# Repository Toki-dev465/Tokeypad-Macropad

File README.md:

# Important Note
My PCB design has a slight error as the 5V on MC is connected to the VCC of OLED. Using 5V may or may not work. It could potentially damage the microcontroller and the OLED. Flashing QMK is a big pain hence I also made CircuitPython KMK firmware. Will definitely try the QMK firmware when I have time. 
# Description
IBM Model M keyboard themed macropad with a rotary encoder for volume control, 6 keys and a 0.91 inch OLED display. 

# Challenges
It was my first ever electronics project. First time using KiCad, Fusion and QMK. I spent many hours just trying to figure out how to do something by Googling and watching tutorials on YouTube. I had to redesign my schematics, PCB and 3D model numerous times. 3D modeling was much harder than I anticipated at first. Even though I made many errors, I believe this shows my learning progress because you can't learn without making mistakes. 

# Specs/BOM

- 1x XIAO RP2040
- 1x SK6812 MINI Led
- 4x M3x16 Bolt
- 4x M3 Heatset
- 6x Cherry MX Switches
- 6x Blank DSA Keycaps
- 1x I2C OLED Display Module 0.91 Inch SSD1306
- 1x Rotary Encoder Module

| Schematic | PCB Design | 3D Model |
| :---: | :---: | :---: |
|  |  |  |
| *Circuit Diagram* | *Top/Bottom Layers* | *Fusion 360 Render* |

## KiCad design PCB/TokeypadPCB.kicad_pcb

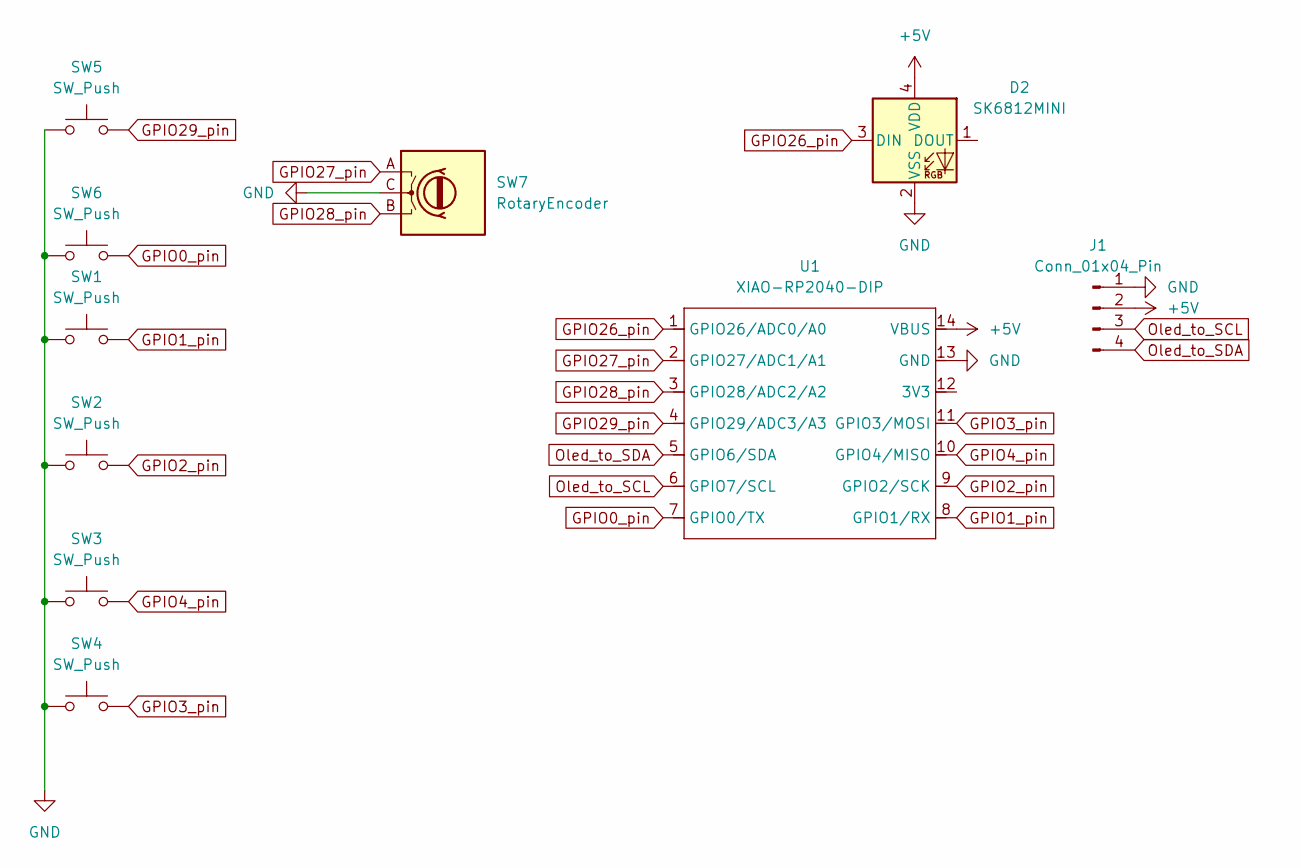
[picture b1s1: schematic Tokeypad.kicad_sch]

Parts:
D2: SK6812MINI; LED_SK6812MINI_PLCC4_3.5x3.5mm_P1.75mm
J1: Conn_01x04_Pin; NS-Tech_Grove_1x04_P2mm_Vertical
SW1, SW2, SW3, SW4, SW5, SW6: SW_Push; SW_Cherry_MX_1.00u_PCB
SW7: RotaryEncoder; RotaryEncoder_Alps_EC11E-Switch_Vertical_H20mm
U1: XIAO-RP2040-DIP

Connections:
+5V: D2.4 (VDD), J1.2, U1.14 (VBUS)
GND: D2.2 (VSS), J1.1, SW1.1, SW2.1, SW3.1, SW4.1, SW5.1, SW6.1, SW7.C, U1.13 (GND)
GPIO0_pin: SW6.2, U1.7 (GPIO0/TX)
GPIO1_pin: SW1.2, U1.8 (GPIO1/RX)
GPIO2_pin: SW2.2, U1.9 (GPIO2/SCK)
GPIO3_pin: SW4.2, U1.11 (GPIO3/MOSI)
GPIO4_pin: SW3.2, U1.10 (GPIO4/MISO)
GPIO26_pin: D2.3 (DIN), U1.1 (GPIO26/ADC0/A0)
GPIO27_pin: SW7.A, U1.2 (GPIO27/ADC1/A1)
GPIO28_pin: SW7.B, U1.3 (GPIO28/ADC2/A2)
GPIO29_pin: SW5.2, U1.4 (GPIO29/ADC3/A3)
Oled_to_SCL: J1.3, U1.6 (GPIO7/SCL)
Oled_to_SDA: J1.4, U1.5 (GPIO6/SDA)

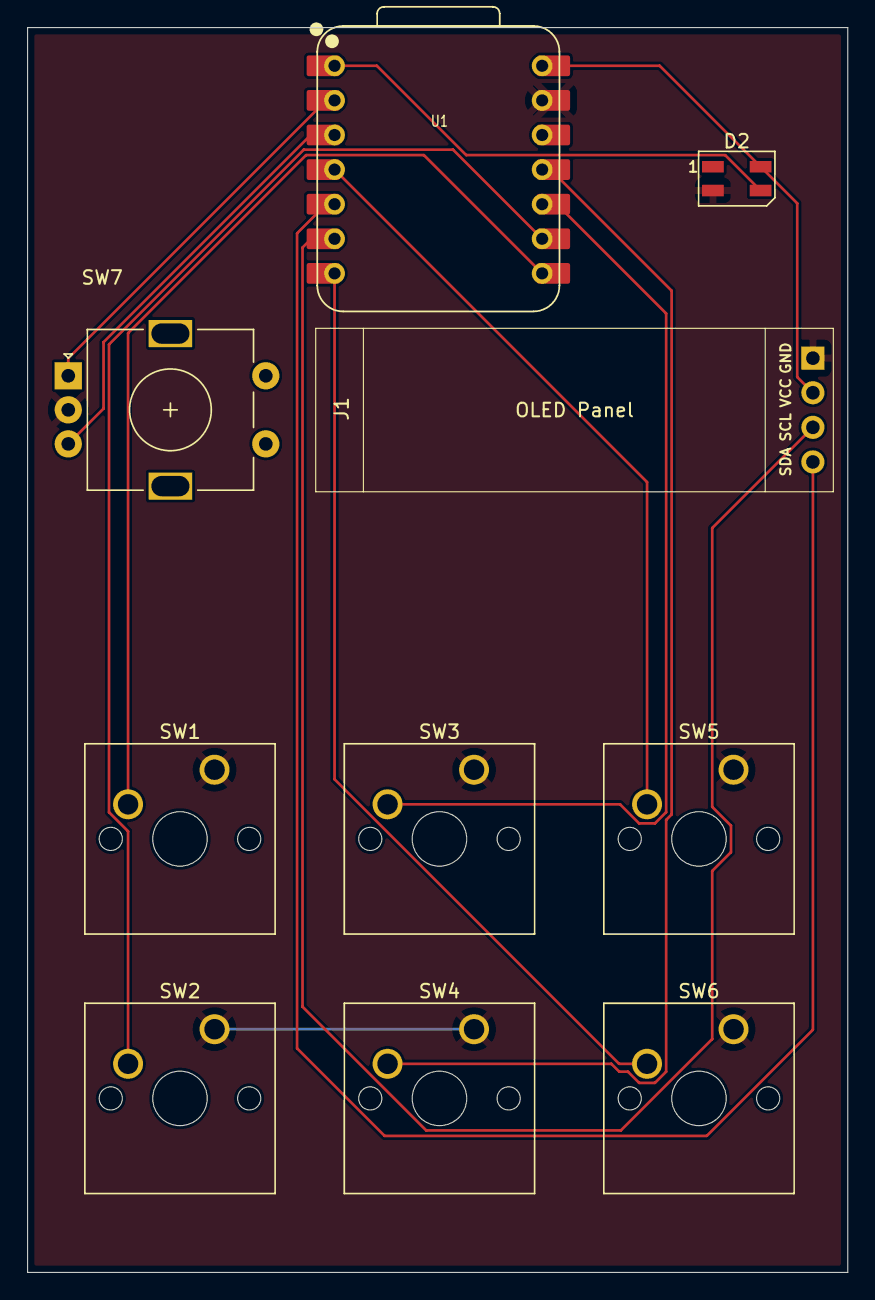
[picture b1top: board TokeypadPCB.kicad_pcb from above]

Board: 2 copper layers, 60.2 x 91.4 mm, 10 parts (0 on the bottom side), 13 nets.

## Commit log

2025-11-21 Create hardware
2025-11-21 Create Schematic
2025-11-21 Rename Screenshot 2025-11-20 224214.png to Hardware/Schematic
2025-11-21 Rename Screenshot 2025-11-20 224214.png to Hardware/Schematic 224214.png
2025-11-21 Rename Screenshot 2025-11-20 224214.png to Schematic.png
2025-11-21 Rename Schematic.png to Hardware/Schematic.png
2025-11-21 Rename Screenshot 2025-11-20 224214.png to Design/sketch.png
2025-11-21 Create Inspiration Model M
2025-12-23 Create Sketch
2025-12-23 Rename Macropad sketch.png to Design/Macropad sketch.png
2025-12-23 Create Design
2025-12-28 Created a new directory for only PCB related files for organization purposes
2026-02-01 Add files via upload
    Fixed version. Holes at the bottom for the screws were unfinished. Made the opening for OLED display smaller.
2026-03-01 Update README with PCB design error clarification
    Clarified the error in PCB design regarding the 5V connection to the OLED.
2026-03-06 Update README with PCB error details and flashing changes
    Expanded note on PCB design error and flashing issues.
2026-03-06 Create CircuitPython_library
